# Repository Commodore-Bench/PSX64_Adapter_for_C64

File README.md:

# PSX64 Adapter for C64

## Introduction

A few years ago I discovered on the homepage of [Synthetic Dreams](http://www.oursyntheticdreams.com/) the [schematic ](http://www.oursyntheticdreams.com/sites/default/files/downloads/psx64schematics.png)and [firmware ](http://www.oursyntheticdreams.com/sites/default/files/downloads/psx64fw11.hex)for a very interesting joystick adapter. With this adapter you can play a game called [Shredz64](https://www.c64-wiki.de/wiki/Shredz64), which is modeled after the Guitar Hero game known from the Playstation 2. I personally didn’t even find that the interesting thing about it, but rather the fact that you could use it to connect the well-known PSX2 gamepads to the C64 for any other game.

Additionally this interface can score with a few additional features:

- Two firebuttons are supported, which is needed for Shredz64 among others
- The analog stick can be used, if of course only digitally
- Since the PSX controller has 4 firebuttons, the above two firebuttons are again assigned with continuous fire.
- You can program macros. So you can store sequences in the adapter and call them up at the push of a button (with the shoulder buttons).
- And an important feature for me personally was that you can play with the PSX2 controllers, which feel very good in my hand.

The PSX64 can, or could, also be ordered as a ready-made unit from Synthetic Dreams. However as a rather large board. And since the delivery is from abroad, with additional fees. What was more obvious than simply rebuilding this adapter. Especially since the website is no longer maintained for almost 5 years and probably the adapter is no longer sold.

Especially since I have now shrunk the adapter so far that it could also be easily installed directly in a PSX2 controller.

The construction is quite simple and could also be built on a strip grid board or a breadboard.

## The construction

I kept the board as compact as possible, but as generous for easy soldering as possible. The components are quite large, for SMD conditions. So that even a little experienced hobbyist should assemble this board quite easily.

For the assembly, besides the board, the following components are needed:

- 2x MCP41100 – SOIC-8 (U1, U2)
- ATMega8-16AU – TQFP-32 (U3)
- 16MHz crystal – 5032 (Y1)
- 4.7µF tantalum capacitor – Kemet A (C1)
- 2x 22pF capacitor – 0805 (C2, C3)
- 100nF capacitor – 0805 (C4)
- 2x 10k resistor – 0805 (R1, R2)
- 2x 1N4004 diode – SMA (D1, D2)

Actually quite manageable and above all also quite cheap. Except for the two digital potentiometers MCP41100, you can get the parts in any well sorted electronics store. The two MCP41100 are available from Mouser, Digikey and sometimes from eBay.

Additionally you need cables for the joystick connections and the corresponding plugs and sockets. For the connection of the PSX2 gamepad I used a PSX extension. You can get them for 2-3 Euro on eBay and they are much cheaper than the jack alone. Just cut the connector and solder it to the board.

For the side to the computer, I used a 10pin ribbon cable, from which I cut off one wire. Then I soldered a standard D-SUB9 socket to it. You could also use a crimp version here.

Since the PSX2 controller is very power hungry, it is not possible to tap the 5V at the C64’s control jacks. I just soldered a wire with a USB connector to it. USB power supplies are nowadays always available in the house and can be used with an external “Power Pack”, i.e. the batteries for charging cell phones, etc..

I used the circuit 1:1, except for the voltage regulator. I left out the voltage regulator, because I wanted to operate the circuit only with 5V anyway. The construction is quite simple, and should start with soldering the ATMega8. Then the two MCP41100 and the crystal. Followed by the two diodes and the remaining capacitors and resistors, the board is populated quite quickly.

## Flashing the firmware

The 6pin connector, shown at the bottom right of the picture, is the ISP interface to load the firmware. A 2-row pin header with 6 pins can be soldered there. The pinout corresponds to the 6pin ISP interface.

Since the firmware is flashed only once, and updates are probably no longer to be expected, I have not soldered the pin header, but only plugged it in and held it a bit tilted during flashing. Certainly not the official procedure, but for extra a pin header was not worth it to me. Especially since I wanted to wrap the board in heat shrink tubing and then the pin header would have only disturbed.

I installed the firmware again with the well known tool “avrdude”. On the website of the manufacturer there are two versions, one for the ATMega8 and then for the ATMega168. But since no features of the ATMega 168 are used, this hardware upgrade is not worthwhile,

I use an AVR ISP MKII for flashing, but any other compatible programming adapter can be used. For my programming adapter the call looks like this:

***`avrdude -c avrispmkII -p m8 -U flash:w:atmega8.hex`***

```
avrdude: AVR device initialized and ready to accept instructions
Reading | ################################################## | 100% 0.00s
avrdude: Device signature = 0x1e9307 (probably m8)avrdude: NOTE: "flash" memory has been specified, an erase cycle will be performed     To disable this feature, specify the -D option.avrdude: erasing chipavrdude: reading input file "atmega8.hex"avrdude: input file atmega8.hex auto detected as Intel Hexavrdude: writing flash (4904 bytes):
Writing | ################################################## | 100% 1.77s
avrdude: 4904 bytes of flash writtenavrdude: verifying flash memory against atmega8.hex:avrdude: load data flash data from input file atmega8.hex:avrdude: input file atmega8.hex auto detected as Intel Hexavrdude: input file atmega8.hex contains 4904 bytesavrdude: reading on-chip flash data:
Reading | ################################################## | 100% 1.36s
avrdude: verifying ...avrdude: 4904 bytes of flash verified
avrdude: safemode: Fuses OK (E:FF, H:D9, L:E1)
avrdude done. Thank you.
```

Now set the fuses so that the external 16MHz crystal can be used:

***`avrdude -c avrispmkII -p m8 -U lfuse:w:0xce:m -U hfuse:w:0xc9:m`***

```
avrdude: AVR device initialized and ready to accept instructions
Reading | ################################################## | 100% 0.00s
avrdude: Device signature = 0x1e9307 (probably m8)avrdude: reading input file "0xce"avrdude: writing lfuse (1 bytes):
Writing | ################################################## | 100% 0.01s
avrdude: 1 bytes of lfuse writtenavrdude: verifying lfuse memory against 0xce:avrdude: load data lfuse data from input file 0xce:avrdude: input file 0xce contains 1 bytesavrdude: reading on-chip lfuse data:
Reading | ################################################## | 100% 0.00s
avrdude: verifying ...avrdude: 1 bytes of lfuse verifiedavrdude: reading input file "0xc9"avrdude: writing hfuse (1 bytes):
Writing | ################################################## | 100% 0.01s
avrdude: 1 bytes of hfuse writtenavrdude: verifying hfuse memory against 0xc9:avrdude: load data hfuse data from input file 0xc9:avrdude: input file 0xc9 contains 1 bytesavrdude: reading on-chip hfuse data:
Reading | ################################################## | 100% 0.00s
avrdude: verifying ...avrdude: 1 bytes of hfuse verified
avrdude: safemode: Fuses OK (E:FF, H:C9, L:CE)
avrdude done. Thank you.
```

This completes the programming and the PSX64 adapter is ready.

I then packed the whole thing completely in heat shrink tubing. If you want to do this in a similar way, you should always remember to put on the heat shrink before the plugs are mounted. Otherwise the tube can not be pulled over, because it would be too small for the plugs.

## Ready

The finished adapter looks like this:

And the whole thing still complete with the two connectors:

As mentioned at the beginning, the board is small enough to be mounted directly into the PSX2 gamepad. But since I still use my gamepads for the PSX2, I chose the external version. Would be happy to see some pictures of it though if anyone is considering installing it.

## BOM

The brands are only representative. Comparable components from other manufacturers can also be used.

|      | Description                                                  | Part                | References | Value             | Footprint                       | Quantity Per PCB |
| ---- | ------------------------------------------------------------ | ------------------- | ---------- | ----------------- | ------------------------------- | ---------------- |
| 1    | Unpolarized capacitor                                        | C                   | C4         | 100n              | C_0805_2012Metric               | 1                |
| 2    | Unpolarized capacitor                                        | C                   | C2 C3      | 22p               | C_0805_2012Metric               | 2                |
| 3    | Polarized capacitor                                          | CP                  | C1         | 4,7µ              | CP_EIA-3216-18_Kemet-A          | 1                |
| 4    | 400V 1A General Purpose Rectifier Diode, DO-41               | 1N4004              | D1 D2      | 1N4004            | D_SMA                           | 2                |
| 5    | Generic connector, single row, 01x02, script generated (kicad-library-utils/schlib/autogen/connector/) | Conn_01x02          | J2         | 5V Power          | PinHeader_1x02_P2.00mm_Vertical | 1                |
| 6    | Generic connector, single row, 01x09, script generated (kicad-library-utils/schlib/autogen/connector/) | Conn_01x09          | J1 J3      | C64 DB9 Connector | PinHeader_1x09_P2.00mm_Vertical | 2                |
| 7    | Generic connector, double row, 02x03, odd/even pin numbering scheme (row 1 odd numbers, row 2 even numbers), script generated (kicad-library-utils/schlib/autogen/connector/) | Conn_02x03_Odd_Even | J4         | ICSP              | PinHeader_2x03_P2.54mm_Vertical | 1                |
| 8    | Resistor                                                     | R                   | R1 R2      | 10k               | R_0805_2012Metric               | 2                |
| 9    | 16MHz, 8kB Flash, 1kB SRAM, 512B EEPROM, TQFP-32             | ATmega8-16AU        | U3         | ATmega8-16AU      | TQFP-32_7x7mm_P0.8mm            | 1                |
| 10   | Single Digital Potentiometer, SPI interface, 256 taps, 100 kohm | MCP41100            | U1 U2      | MCP41100          | SOIC-8_3.9x4.9mm_P1.27mm        | 2                |
| 11   | Two pin crystal                                              | Crystal             | Y1         | 16MHz             | Crystal_SMD_5032-2Pin_5.0x3.2mm | 1                |

## PCB

The PCB can either be ordered directly from [PCBWay](https://www.pcbway.com/project/shareproject/PSX64_Adapter_for_C64.html), or you can create it yourself from the Gerber files available here.

If you liked my project, I would be very happy about a small coffee donation.

# License

The contents of this repository, with the exception of the Docs and Software directories, are released under the following license:

- the "Creative Commons Attribution-NonCommercial-ShareAlike 4.0 International License" (CC BY-NC-SA 4.0) full text of this license is included in the [LICENSE.CC-NC-BY-SA-4.0](https://github.com/DL2DW/PSX64_Adapter_for_C64/blob/main/LICENSE.CC-NC-BY-SA) file and a copy can also be found at https://creativecommons.org/licenses/by-nc-sa/4.0/

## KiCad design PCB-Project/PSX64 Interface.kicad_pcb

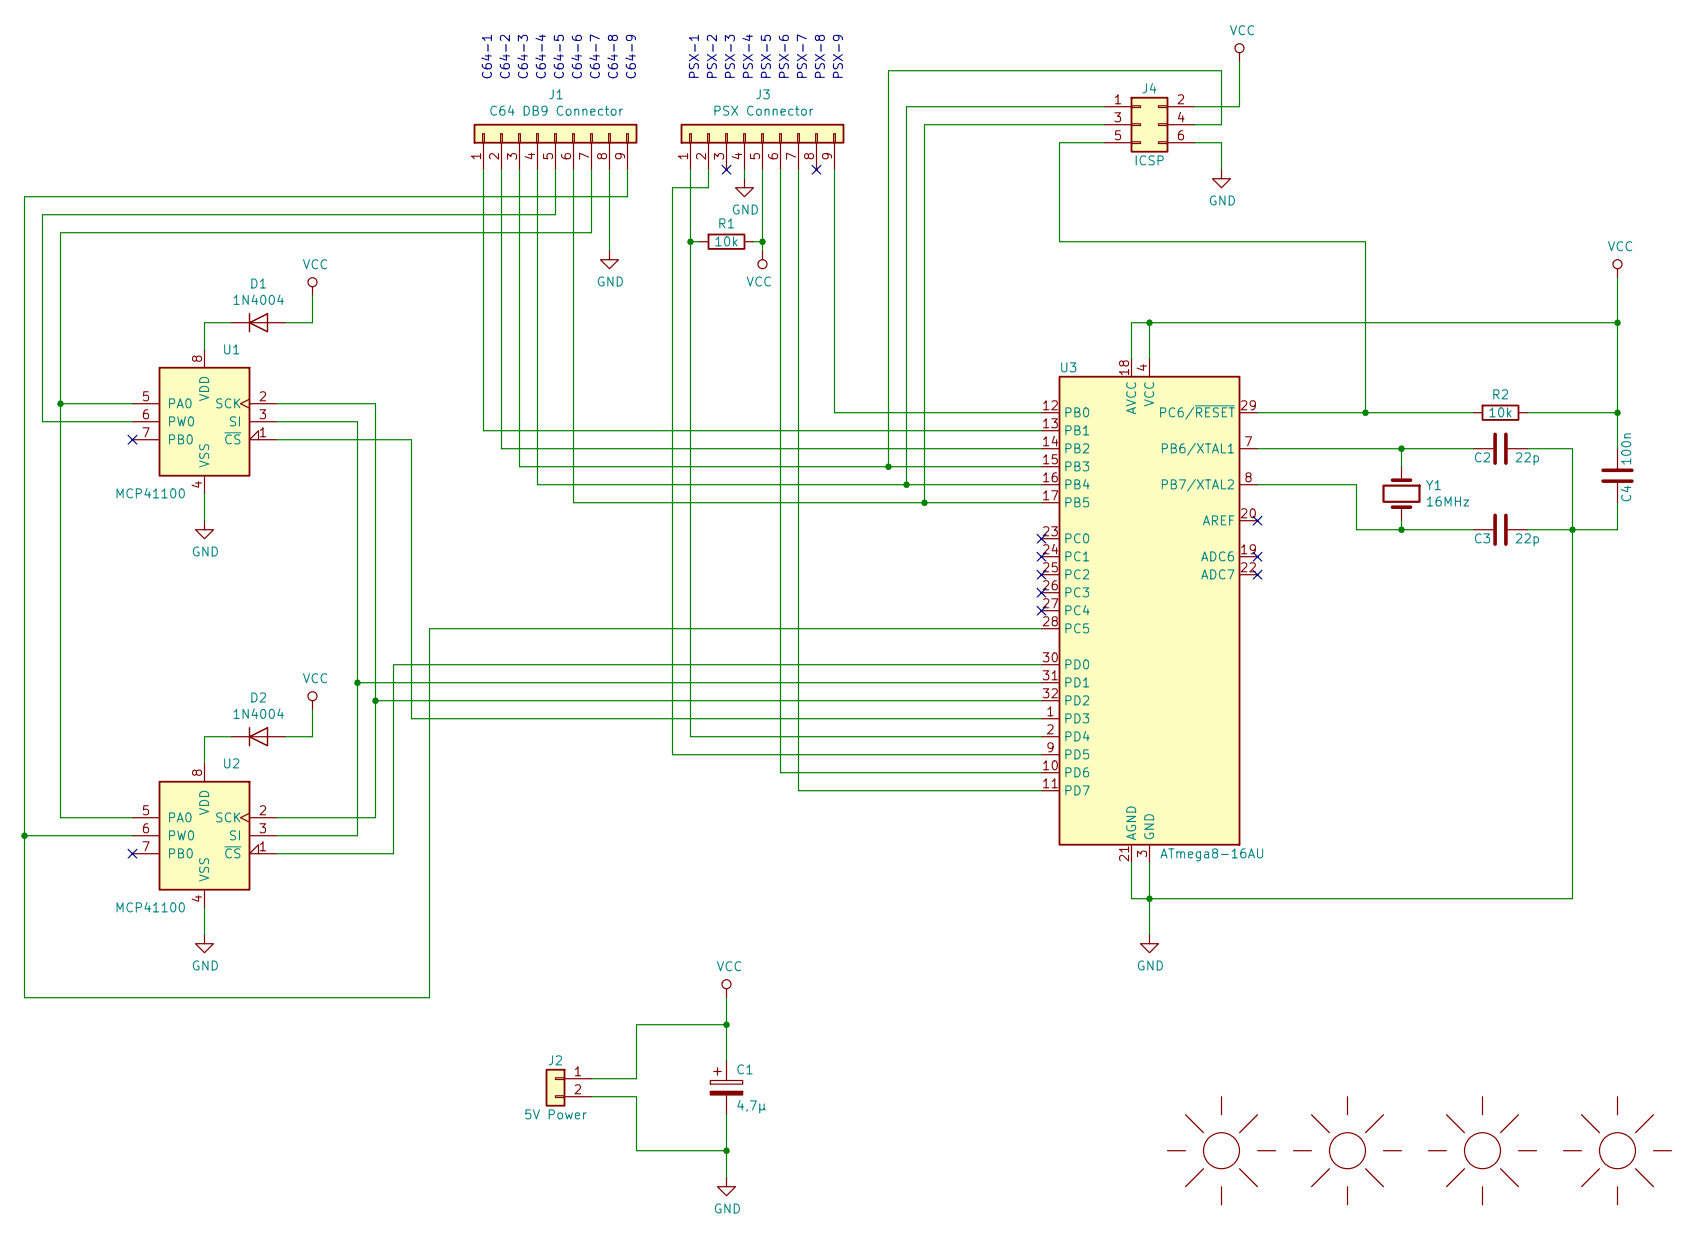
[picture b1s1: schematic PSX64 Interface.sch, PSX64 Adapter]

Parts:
C1: 4,7µ; CP_EIA-3216-18_Kemet-A
C2, C3: 22p; C_0805_2012Metric
C4: 100n; C_0805_2012Metric
D1, D2: 1N4004; D_SMA
J1: C64 DB9 Connector; PinHeader_1x09_P2.00mm_Vertical
J2: 5V Power; PinHeader_1x02_P2.00mm_Vertical
J3: PSX Connector; PinHeader_1x09_P2.00mm_Vertical
J4: ICSP; PinHeader_2x03_P2.54mm_Vertical
M1: SUNLOGO; Logo_silk_CC-BY-NC-SA_5x2mm
M2: SUNLOGO; KiCad-Logo2_5mm_SilkScreen
M3: SUNLOGO; Logo_silk_OSHW_6x6mm
M4: SUNLOGO; DL2DW_Logo_Silk_10x5mm
R1, R2: 10k; R_0805_2012Metric
U1, U2: MCP41100; SOIC-8_3.9x4.9mm_P1.27mm
U3: ATmega8-16AU; TQFP-32_7x7mm_P0.8mm
Y1: 16MHz; Crystal_SMD_5032-2Pin_5.0x3.2mm

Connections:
GND: C1.2, C2.1, C3.1, C4.2, J1.8, J2.2, J3.4, J4.6, U1.4 (VSS), U2.4 (VSS), U3.3 (GND), U3.5 (GND), U3.21 (AGND)
unnamed: C2.2, U3.7 (PB6/XTAL1), Y1.1
unnamed: C3.2, U3.8 (PB7/XTAL2), Y1.2
unnamed: D1.1 (K), U1.8 (VDD)
unnamed: D2.1 (K), U2.8 (VDD)
unnamed: J1.1, U3.13 (PB1)
unnamed: J1.2, U3.14 (PB2)
unnamed: J1.3, J4.4, U3.15 (PB3)
unnamed: J1.4, J4.1, U3.16 (PB4)
unnamed: J1.5, U1.6 (PW0)
unnamed: J1.6, J4.3, U3.17 (PB5)
unnamed: J1.7, U1.5 (PA0), U2.5 (PA0)
unnamed: J1.9, U2.6 (PW0), U3.28 (PC5)
unnamed: J3.1, R1.2, U3.2 (PD4)
unnamed: J3.2, U3.9 (PD5)
unnamed: J3.6, U3.10 (PD6)
unnamed: J3.7, U3.11 (PD7)
unnamed: J3.9, U3.12 (PB0)
unnamed: J4.5, R2.2, U3.29 (PC6/~RESET)
unnamed: U1.1 (~CS), U3.1 (PD3)
unnamed: U1.2 (SCK), U2.2 (SCK), U3.32 (PD2)
unnamed: U1.3 (SI), U2.3 (SI), U3.31 (PD1)
unnamed: U2.1 (~CS), U3.30 (PD0)
VCC: C1.1, C4.1, D1.2 (A), D2.2 (A), J2.1, J3.5, J4.2, R1.1, R2.1, U3.4 (VCC), U3.6 (VCC), U3.18 (AVCC)

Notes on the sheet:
C64-1
C64-2
C64-3
C64-4
C64-5
C64-6
C64-7
C64-8
C64-9
PSX-1
PSX-2
PSX-3
PSX-4
PSX-5
PSX-6
PSX-7
PSX-8
PSX-9

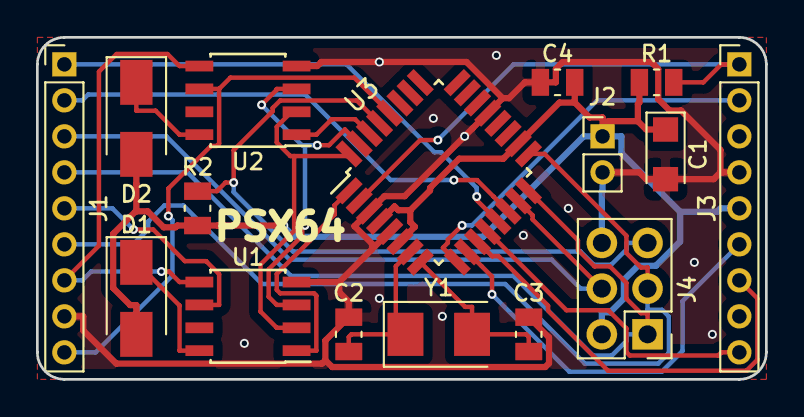
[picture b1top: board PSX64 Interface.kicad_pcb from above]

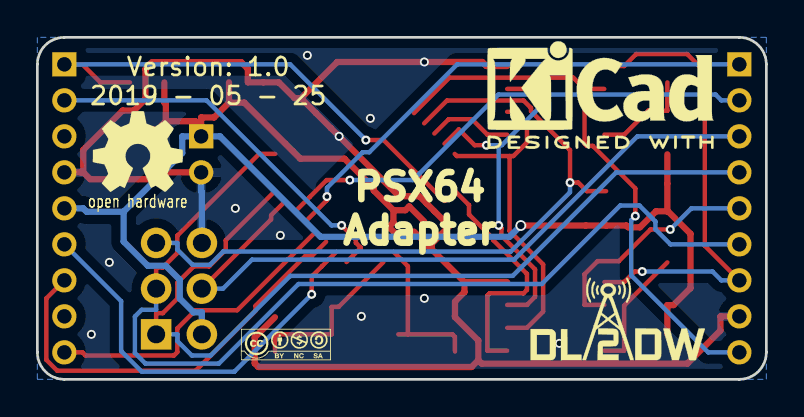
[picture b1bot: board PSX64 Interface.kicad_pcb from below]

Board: 2 copper layers, 40.5 x 19.0 mm, 20 parts (4 on the bottom side), 24 nets.

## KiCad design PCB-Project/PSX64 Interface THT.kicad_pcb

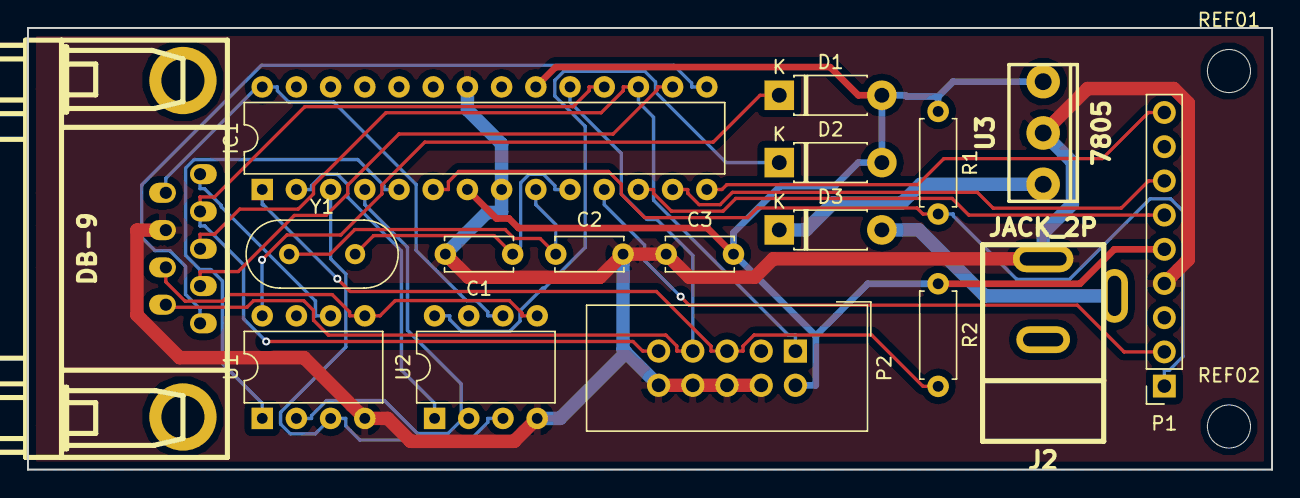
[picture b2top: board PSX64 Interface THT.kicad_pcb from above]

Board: 2 copper layers, 92.4 x 32.8 mm, 19 parts (0 on the bottom side), 26 nets.

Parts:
C1, C2: 22p; C_Disc_D5.0mm_W2.5mm_P5.00mm
C3: 100n; C_Disc_D5.0mm_W2.5mm_P5.00mm
D1, D2, D3: 1N4004; D_DO-41_SOD81_P7.62mm_Horizontal
IC1: ATMEGA168-P; DIP-28_W7.62mm
J1: DB-9; DB_9F
J2: JACK_2P; dc_socket
P1: PSX Controller; PinSocket_1x09_P2.54mm_Vertical
P2: AVR ISCP; IDC-Header_2x05_P2.54mm_Vertical
R1, R2: 10k; R_Axial_DIN0207_L6.3mm_D2.5mm_P7.62mm_Horizontal
REF01, REF02: MountingHole_3.2mm_M3_DIN965
U1, U2: MCP41100; DIP-8_W7.62mm
U3: 7805; to220
Y1: Crystal; Crystal_HC18-U_Vertical

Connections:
GND: C1.2, C2.2, C3.1, IC1.8, IC1.22, J1.8, J2.3, P1.4, P2.4, P2.6, P2.8, P2.10, U1.4, U2.4, U3.2
unnamed: C1.1, IC1.10, Y1.2
unnamed: C2.1, IC1.9, Y1.1
unnamed: D1.1, U1.8
unnamed: D2.1, U2.8
unnamed: D3.1, U3.1
unnamed: D3.2, J2.1
unnamed: IC1.1, P2.5, R2.2
unnamed: IC1.2, U2.1
unnamed: IC1.3, U1.3, U2.3
unnamed: IC1.4, U1.2, U2.2
unnamed: IC1.5, U1.1
unnamed: IC1.6, P1.1, R1.2
unnamed: IC1.11, P1.2
unnamed: IC1.12, P1.6
unnamed: IC1.13, P1.7
unnamed: IC1.14, P1.9
unnamed: IC1.15, J1.1
unnamed: IC1.16, J1.2
unnamed: IC1.17, J1.3, P2.1
unnamed: IC1.18, J1.4, P2.9
unnamed: IC1.19, J1.6, P2.7
unnamed: IC1.28, J1.9, U2.6
unnamed: J1.5, U1.6
unnamed: J1.7, U1.5, U2.5
VCC: C3.2, D1.2, D2.2, IC1.7, IC1.20, P1.5, P2.2, R1.1, R2.1, U3.3

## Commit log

2021-03-30 PCB order link added
